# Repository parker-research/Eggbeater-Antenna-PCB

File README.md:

# Eggbeater Antenna PCB

An open KiCad re-implementation of a **PCB quadrature phasing feed for Egg Beater satellite antennas**. It works with two loops, a turnstile, or any other pair of balanced 100 Ω elements that need to be fed 90° apart.

The design is **inspired by and mechanically equivalent to the [Halibut Electronics EggNOGS](https://electronics.halibut.com/product/eggnogs/) kit**. It was reverse-engineered from the public product photos and the [EggNOGS Assembly Guide](https://halibut-electronics.github.io/EggNOGS/EggNOGS%20Assembly.pdf). No original design files were used. The transmission line, stackup and all dimensions were derived independently (see [Design](#design)). If you just want an antenna, buy the kit from Halibut Electronics and support the people who came up with the idea.

| Main board (UP side) | Main board (DOWN side) |
|---|---|
|  |  |

| Phasing board, front (ferrite side) | Phasing board, back (center-pin side) |
|---|---|
|  |  |

---

## How it works

```
 coax feed ─► edge SMA/BNC/F ─► CMCC balun ─┬─► direct path   (L)        ─► tab 1 ─► loop "A" bolts
 (50 Ω)                       RG-316 through │
                              BN-43-3312     └─► delayed path (L + λ/4)  ─► tab 2 ─► loop "B" bolts
                                   100 Ω balanced, shielded stripline (2 × 100 Ω in parallel = 50 Ω)
```

* **Balun / common-mode current choke:** a U of RG-316 passes once through a BN-43-3312 binocular core. The input end connects to the feed connector. At the output end, the braid and the center conductor become the two balanced conductors, `LINE_P` and `LINE_N`.
* **Phasing line:** a 100 Ω **balanced and shielded** transmission line built inside the 4-layer phasing board.
  * The two conductors are stacked on top of each other: `LINE_P` on In1.Cu and `LINE_N` on In2.Cu (a broadside-coupled pair).
  * Solid GND planes on F.Cu and B.Cu form the shield, closed at the sides by via fences.
  * The line splits right at the balun into two paths. The delayed path is 81.2 mm longer, which is one quarter wavelength at 436.5 MHz inside the board. Each loop presents 100 Ω and terminates its own 100 Ω line, so the two paths in parallel present 50 Ω to the balun.
* **Main board:** two slots take the phasing board's tabs at 90°. Traces run from the slot pads to four No. 8 bolts, and the two loops attach across opposite bolts (A–A and B–B).
* **Polarization select:** flipping the phasing board 180° before soldering swaps which loop gets the delayed feed, which switches between RHCP and LHCP. The phasing board's long edges are labeled `RHCP →` and `LHCP →`. Whichever label sits at the **SELECT POLARIZATION** mark on the main board's DOWN side is the polarization you get.

---

## Repository layout

```
kicad/main_board/        main_board.kicad_pro / .kicad_pcb       (2-layer, Ø58 mm)
kicad/phasing_board/     phasing_board.kicad_pro / .kicad_pcb    (4-layer, 436.5 MHz)
fab/*/                   *_gerbers.zip  (Gerber X2 + Excellon, ready to upload to JLCPCB)
scripts/generate_boards.py   parametric generator (Python stdlib only)
scripts/stripline_solver.py  2-D field solver used to size the line (numpy + scipy)
scripts/build.sh             generate → upgrade → refill zones → DRC → gerbers → renders
docs/img/                    3-D renders
```

The boards are generated by `scripts/generate_boards.py`, and every dimension is a named constant there. Rebuild with:

```sh
./scripts/build.sh            # default 436.5 MHz
./scripts/build.sh 145.9      # e.g. a 2 m phasing board (the meander grows automatically)
```

This needs KiCad ≥ 9 (`kicad-cli`) and Python 3. The generator also fits 145.9 MHz and 137.5 MHz on the same 30 × 99 mm board, using seven meanders instead of two. Only the 436.5 MHz board is committed and DRC-checked. There is no schematic: these are transmission-line boards defined entirely by their layout, like the original.

---

## Design

### Phasing board transmission line

JLCPCB **JLC04161H-7628** stackup, 1.6 mm:

| Layer | Thickness | Use |
|---|---|---|
| F.Cu (1 oz) | 0.035 | GND shield, CMCC braid pads, tab pads (front) |
| 7628 prepreg, εr 4.4 | 0.2104 | |
| In1.Cu (0.5 oz) | 0.0152 | `LINE_P`, 0.25 mm |
| Core, εr 4.6 | 1.065 | |
| In2.Cu (0.5 oz) | 0.0152 | `LINE_N`, 0.25 mm (directly under `LINE_P`) |
| 7628 prepreg, εr 4.4 | 0.2104 | |
| B.Cu (1 oz) | 0.035 | GND shield, CMCC center pads, feed center pad, tab pads (back) |

`scripts/stripline_solver.py` is a finite-volume Laplace solver. It matches the exact stripline formula to within 0.5%. With the inner GND pour kept 1 mm back from the traces, it gives:

| Trace width | Z<sub>diff</sub> | Z<sub>common</sub> | ε<sub>eff</sub> |
|---|---|---|---|
| 0.25 mm | **100.0 Ω** | 27.8 Ω | 4.476 |

The quarter-wave delay is `c / (4 · f · √εeff)` = **81.16 mm** at 436.5 MHz. As generated, the direct path is 82.53 mm and the delayed path is 163.69 mm, a difference of **81.16 mm**. Both paths share identical fan-outs, vias and tab pads, so those parts cancel out of the phase difference. FR-4 εr tolerance (±5%) moves the phase by only about ±4°.

### Mechanical interface

| Item | Value |
|---|---|
| Main board | Ø 58 mm, fits inside a 2 in Sch 40 PVC cap (~60.3 mm ID) |
| Bolt holes | 4 × Ø 4.3 mm plated, Ø 9 mm pads, on a Ø 46 mm circle at 45° to the slots (32.5 mm square) |
| Slots | 2 × 1.8 × 8.4 mm, centers ±5 mm, 3 + 3 plated pads each at 2.2 mm pitch |
| Phasing board | 30 × 99 mm overall (95.8 mm body + two 7 × 3.2 mm tabs), kept under 100 mm for JLCPCB's cheapest size tier, with shoulder relief notches so the tabs seat flush |
| Tab protrusion | 1.6 mm above the UP side of the main board, which gives solder fillets on both faces |
| CMCC holes | 2 × Ø 1.8 mm **non-plated** (see note in step 1 of assembly) |

### Differences from the original

* The line geometry, stackup, board sizes and pad sizes are all independently derived. They are not copies.
* The CMCC feed-through holes are **NPTH by design**, and copper is pulled back from them. That avoids the plated-hole short described in the original guide's 2025-12 errata.
* The tabs have relief notches, so the router's corner radius can't hold the boards apart.
* One universal feed-connector footprint takes an SMA, BNC or Type-F edge-mount jack.
* The generator is parametric in frequency.
* No right-angle assembly jig is included. Use the hand method described below.

---

## Ordering (JLCPCB)

**Main board** (`fab/main_board/main_board_gerbers.zip`), basic options throughout:
2 layers · FR-4 · 1.6 mm · 1 oz · HASL (lead-free) · any color · "Remove order number" at your preference.
The two slots are in the board outline (Edge.Cuts), so no extra slot option is needed.

**Phasing board** (`fab/phasing_board/phasing_board_gerbers.zip`):
4 layers · FR-4 · 1.6 mm · outer 1 oz / inner 0.5 oz · HASL (lead-free) · **Impedance control: Yes → stackup JLC04161H-7628**.
The 0.25 mm line width was computed for that stackup. Choosing it pins the dielectric thicknesses that the 100 Ω and the λ/4 length depend on. Via 0.3/0.6 mm, minimum track 0.25 mm and minimum clearance 0.2 mm are all within JLC's standard capabilities.

There is no SMT assembly: everything is hand-soldered.

---

## Bill of Materials

### Boards & RF parts

| Qty | Part | Notes |
|---|---|---|
| 1 | Main board PCB | `fab/main_board` |
| 1 | Phasing board PCB, 436.5 MHz | `fab/phasing_board` |
| 1 | Ferrite binocular core **BN-43-3312** (Fair-Rite **2843010302**) | 25.4 × 19.4 × 9.5 mm, mix 43 |
| ~24 cm | **RG-316** coax, no connectors | Enough for one retry. About 10 cm is used. |
| 1 | Edge-mount jack for 1.6 mm (0.062") PCB: **SMA female** (e.g. Amphenol 132289 or a generic "SMA-KE 1.6 mm"), *or* BNC edge-mount, *or* Type-F edge-mount | All three fit the same footprint |
| 1 | Cable tie, ~2.5 × 100–150 mm, UV-resistant | Holds the ferrite to the board |

### Mounting hardware (18-8 stainless)

| Qty | Part |
|---|---|
| 4 | No. 8-32 × 1" machine screws (M4 × 25 mm also fits the 4.3 mm holes) |
| 4 | No. 8 split lock washers |
| 12 | No. 8-32 hex nuts |
| 4 | No. 8-32 nylon-insert lock nuts |
| 8 | No. 8 flat washers |
| 4 | No. 8 rubber / EPDM sealing washers |
| 1 | 2 in (50 mm) Sch 40 PVC cap, with four holes drilled on a Ø 46 mm circle (32.5 mm square), 11/64" (4.4 mm) or 3/16" drill |

### You also provide

* 2 in / 50 mm Sch 40 PVC pipe for the mast.
* Loop material, e.g. 14 AWG solid copper stripped from Romex (about 2 × 80 cm at 436 MHz).
* Optionally a "ground reflector" under the loops.
* Feed line and radio.

### Tools

Soldering iron with enough power for the connector, solder, flush cutters, and wire strippers (14 and 20–22 AWG round holes work well on RG-316). You'll also want a No. 2 Phillips screwdriver, an 11/32" nut driver, a multimeter, and a drill for the PVC cap.

---

## Assembly Instructions

Faces of the phasing board:
* **Front (F):** the side with the ferrite outline and the `SHIELD` / `IN` / `OUT` labels.
* **Back (B):** the side with the `CENTER` labels and the connector's center-pin pad.

### 1. Inspect the phasing board

The two CMCC holes are **non-plated**: the hole walls should look like bare fiberglass. If your fab plated them anyway, drill them out with a 1.8–2.0 mm (5/64"–3/32") bit. Otherwise the braid can short to the center pad.

### 2. Build the common-mode choke (the fiddly part)

1. Bend the RG-316 into a U and push both ends through the two holes of the BN-43-3312, until the bend sits against the core. Leave the extra length on one end.
2. Trim both ends so about **20 mm** sticks out of the core.
3. On each end, strip about **8 mm** of the outer jacket.
4. Comb the braid back, gather it to one side and twist it into a pigtail that sticks out at 90°. Keep the braid flat against the dielectric so it will sit flush on the board. Point both pigtails the same way.
5. Cut the dielectric about **1.6–2 mm** past the braid (one board thickness, erring long), then strip it to expose the center conductor.
6. From the **front**, push both ends through the CMCC holes. The pigtails lie on the two `SHIELD` pads and point toward the feed connector. Leave about 9–12 mm of coax between the board and the core so the core can later fold flat without kinking the cable.
7. On the **back**, bend each center conductor over onto the adjacent `CENTER` pad and solder it.
8. On the **front**, solder each braid pigtail to its `SHIELD` pad.

   **Warning:** the two shields are **electrically different**. The `IN` shield pad is ground. The `OUT` shield pad is an isolated island and is one side of the balanced line. Do not bridge them to each other or to the ground plane: that bypasses the choke.
9. Fold the core flat onto its silkscreen outline and strap it down with the cable tie. The tie goes around the board, between the tick marks. This is also your chance to even out the U-bend.

### 3. Feed connector

Slide the SMA, BNC or F edge-mount jack onto the end of the board, with its **center pin on the back-side center pad**.

1. Solder the center pin first. Reflow it and adjust until the jack sits straight.
2. Solder all ground legs, front and back.

The jack has a lot of thermal mass, so use a hot iron and be patient. Let it cool before moving on.

### 4. Quick continuity check (multimeter)

| Probe | Expected |
|---|---|
| Connector shell ↔ outer tab pads | short (ground) |
| Connector shell ↔ **front** middle tab pads (`LINE_P`) | short (through the RG-316 braid, which is normal) |
| Connector center ↔ **back** middle tab pads (`LINE_N`) | short (through the RG-316 center conductor) |
| Connector center ↔ shell | **open**. It becomes a short once the loops are attached, which is normal for loops. |
| `IN` shield pad ↔ `OUT` shield pad on the copper *around* them | no solder bridge |

### 5. Choose the polarization and mate the boards

Most amateur satellites use **RHCP**; use that unless you know otherwise.

1. Find the **THIS SIDE DOWN** face of the main board. The phasing board goes in from this side, and its tabs poke out of the **THIS SIDE UP** face.
2. Turn the phasing board so that the edge labeled with the polarization you want (`RHCP →` or `LHCP →`) is next to the **SELECT POLARIZATION** mark.
3. Push both tabs fully into the slots. The shoulders must sit flat against the main board with no gap, and the tab tips stick out about 1.6 mm on the UP side.
4. Holding the boards at 90°, tack-solder **one outer pad** only.
5. Check the angle with a square. If it needs adjusting, re-heat that joint and move the board. Don't bend a cold joint, or you'll lift the pad. The feed line hangs from this joint for the life of the antenna, so get it as square as you can.
6. Solder all 12 pad pairs on the **UP** side, then all 12 on the **DOWN** side. Each pad on the main board should fillet onto the facing pad of the tab.

The polarization sense was derived from the geometry, assuming loop A leads, loop B lags, and radiation toward the UP side (the sky). If a pass shows the opposite sense, that is the one thing to double-check. The fix is to build the next one flipped.

### 6. Mount in the PVC cap

Repeat for each of the four bolts, from inside to outside:

```
screw head ─ split lock washer ─ MAIN BOARD ─ nut ─ (PVC cap wall) ─ rubber sealing washer ─ nut
           ─ flat washer ─ LOOP TERMINAL ─ flat washer ─ nut (plain while tuning, nylon lock nut when deployed)
```

1. Put a lock washer on the screw and insert it from the **DOWN** side of the main board. Tighten a nut on the UP side just enough to flatten the lock washer. Don't crush the board.
2. Push the assembly into the cap so the four screws come out through the drilled holes.
3. Add the rubber sealing washers and nuts, and tighten to seal without crushing. This joint is both the weather seal and the structural mount.
4. Add a flat washer, the loop, and another flat washer. Finish with a plain nut while tuning, and swap to a nylon lock nut once you're finished.

### 7. Loops

Loop A connects across the two bolts marked **A**, and loop B across the two marked **B**. These are opposite bolts, so the two loops end up at 90° to each other. The main board's UP side is silkscreened with the letters.

The recommended loop design is the **K5OE rectangular Egg Beater**: two rectangular "full-wave" loops, each about 10.7% longer than one wavelength, with a 45:55 ratio between the horizontal and vertical sides. The open ends of each loop are at the center of the bottom side, where it meets the bolts.

| | Formula (f in MHz) | 436.5 MHz |
|---|---|---|
| Top & bottom | 7464.8 / f cm | 17.1 cm |
| Sides | 9123.6 / f cm | 20.9 cm |

Several builders report that these dimensions resonate high, around 465 MHz. Consider building about **+7% larger** (18.3 × 22.4 cm at 436.5 MHz) and trimming down. Lay each loop across its two bolts, mark where they cross, strip the wire past that point, and wrap it 180° around the bolt between the flat washers.

See K5OE's original Egg Beater II write-up for background. The same feed also drives turnstiles, circular Egg Beaters and quadrifilar helices. Avoid designs that get their 90° by making the two loops different sizes: this feed already supplies the 90° itself.

### 8. Deploying

* Keep the feed line from swinging: it hangs from the board joints. Use a short, flexible jumper, and zip-tie the cable to the mast about 15 cm below the cap.
* Plug the bottom of the mast against critters, but leave a weep hole for condensation.
* Transmit power has **not been tested** on this design. The line is 0.25 mm, 0.5 oz inner copper, so stay conservative (a few watts) until you've verified it. The original kit is rated at 5–10 W with confidence.

---

## Credits

* Concept, mechanical arrangement, and the assembly and loop guidance adapted above: **Mark (N6MTS), Halibut Electronics**. See the [EggNOGS kit](https://electronics.halibut.com/product/eggnogs/) and the [EggNOGS Assembly Guide](https://halibut-electronics.github.io/EggNOGS/EggNOGS%20Assembly.pdf).
* Rectangular Egg Beater loop dimensions: **Jerry, K5OE**.

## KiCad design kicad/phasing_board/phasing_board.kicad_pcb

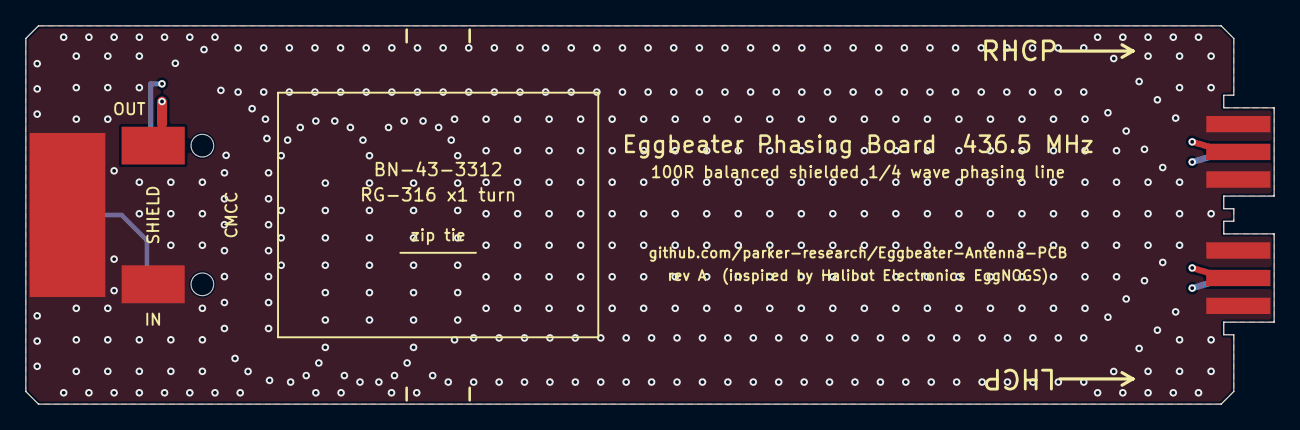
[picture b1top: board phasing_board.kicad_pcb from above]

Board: 4 copper layers, 99.0 x 30.0 mm, 4 parts (0 on the bottom side), 4 nets.

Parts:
J1: EdgeLaunch_SMA_BNC_F_1.6mm
L1: CMCC_RG316_BN-43-3312
P1: PhasingTab_TAB1
P2: PhasingTab_TAB2

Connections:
GND: J1.2, L1.2, P1.1, P1.3, P1.4, P1.6, P2.1, P2.3, P2.4, P2.6
LINE_N: L1.3, P1.5, P2.5
LINE_P: L1.4, P1.2, P2.2
RF_IN: J1.1, L1.1

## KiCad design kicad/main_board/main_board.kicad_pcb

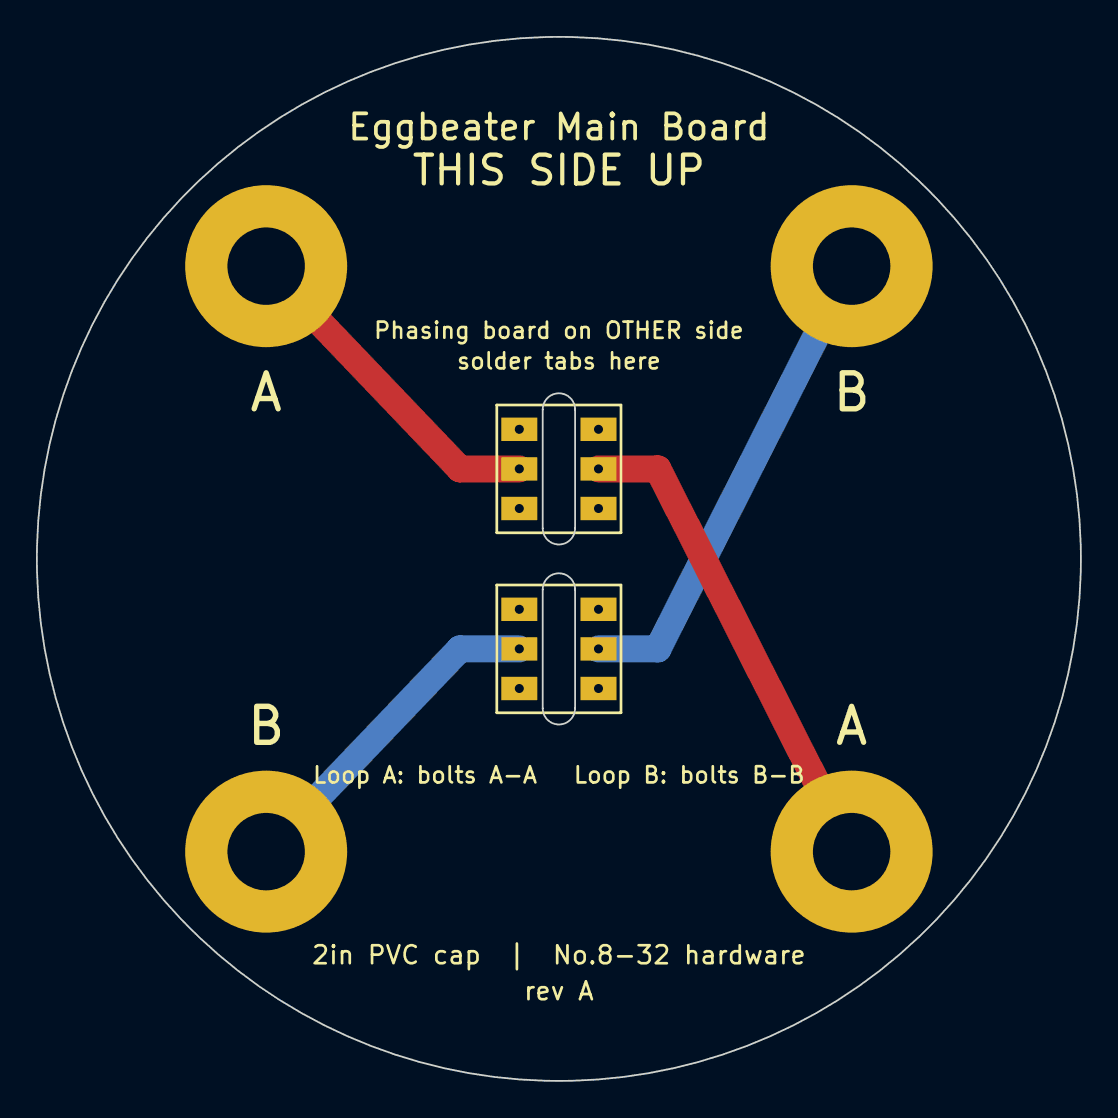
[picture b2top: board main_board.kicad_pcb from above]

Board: 2 copper layers, 58.0 x 58.0 mm, 6 parts (0 on the bottom side), 4 nets.

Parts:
H1, H2, H3, H4: MountingHole_4.3mm_No8_Pad9mm
S1, S2: PhasingBoard_Slot_1.8x8.4mm

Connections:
LOOP_A1: H1.1, S1.2
LOOP_A2: H4.1, S1.5
LOOP_B1: H3.1, S2.2
LOOP_B2: H2.1, S2.5
